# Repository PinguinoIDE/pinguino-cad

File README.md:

Most of the Pinguino boards or extensions are designed with Kicad.

KiCad is an EDA software suite for the creation of professional schematics and printed circuit boards up to 16 layers. KiCad runs on Windows, Linux and Apple OS X and is released under the open-source GNU GPL v2 free of charge. With Kicad you can do the following :

<ul>
<li>Schematic design.
<li>Netlist creation in multiple formats (PCBNew, OrCAD, CadStar, Spice, etc...).
<li>PCB design
<li>3D visualization of your PCB
<li>Fabrication outputs generation (Gerber, drill files and whatever can be needed to manufacture a PCB.)
</ul>

For a more detailed explanation please refer to the official site : http://www.kicad.org

For a better result we use libraries, modules en 3D packages from Walter : http://smisioto.no-ip.org/elettronica/kicad/kicad-en.htm

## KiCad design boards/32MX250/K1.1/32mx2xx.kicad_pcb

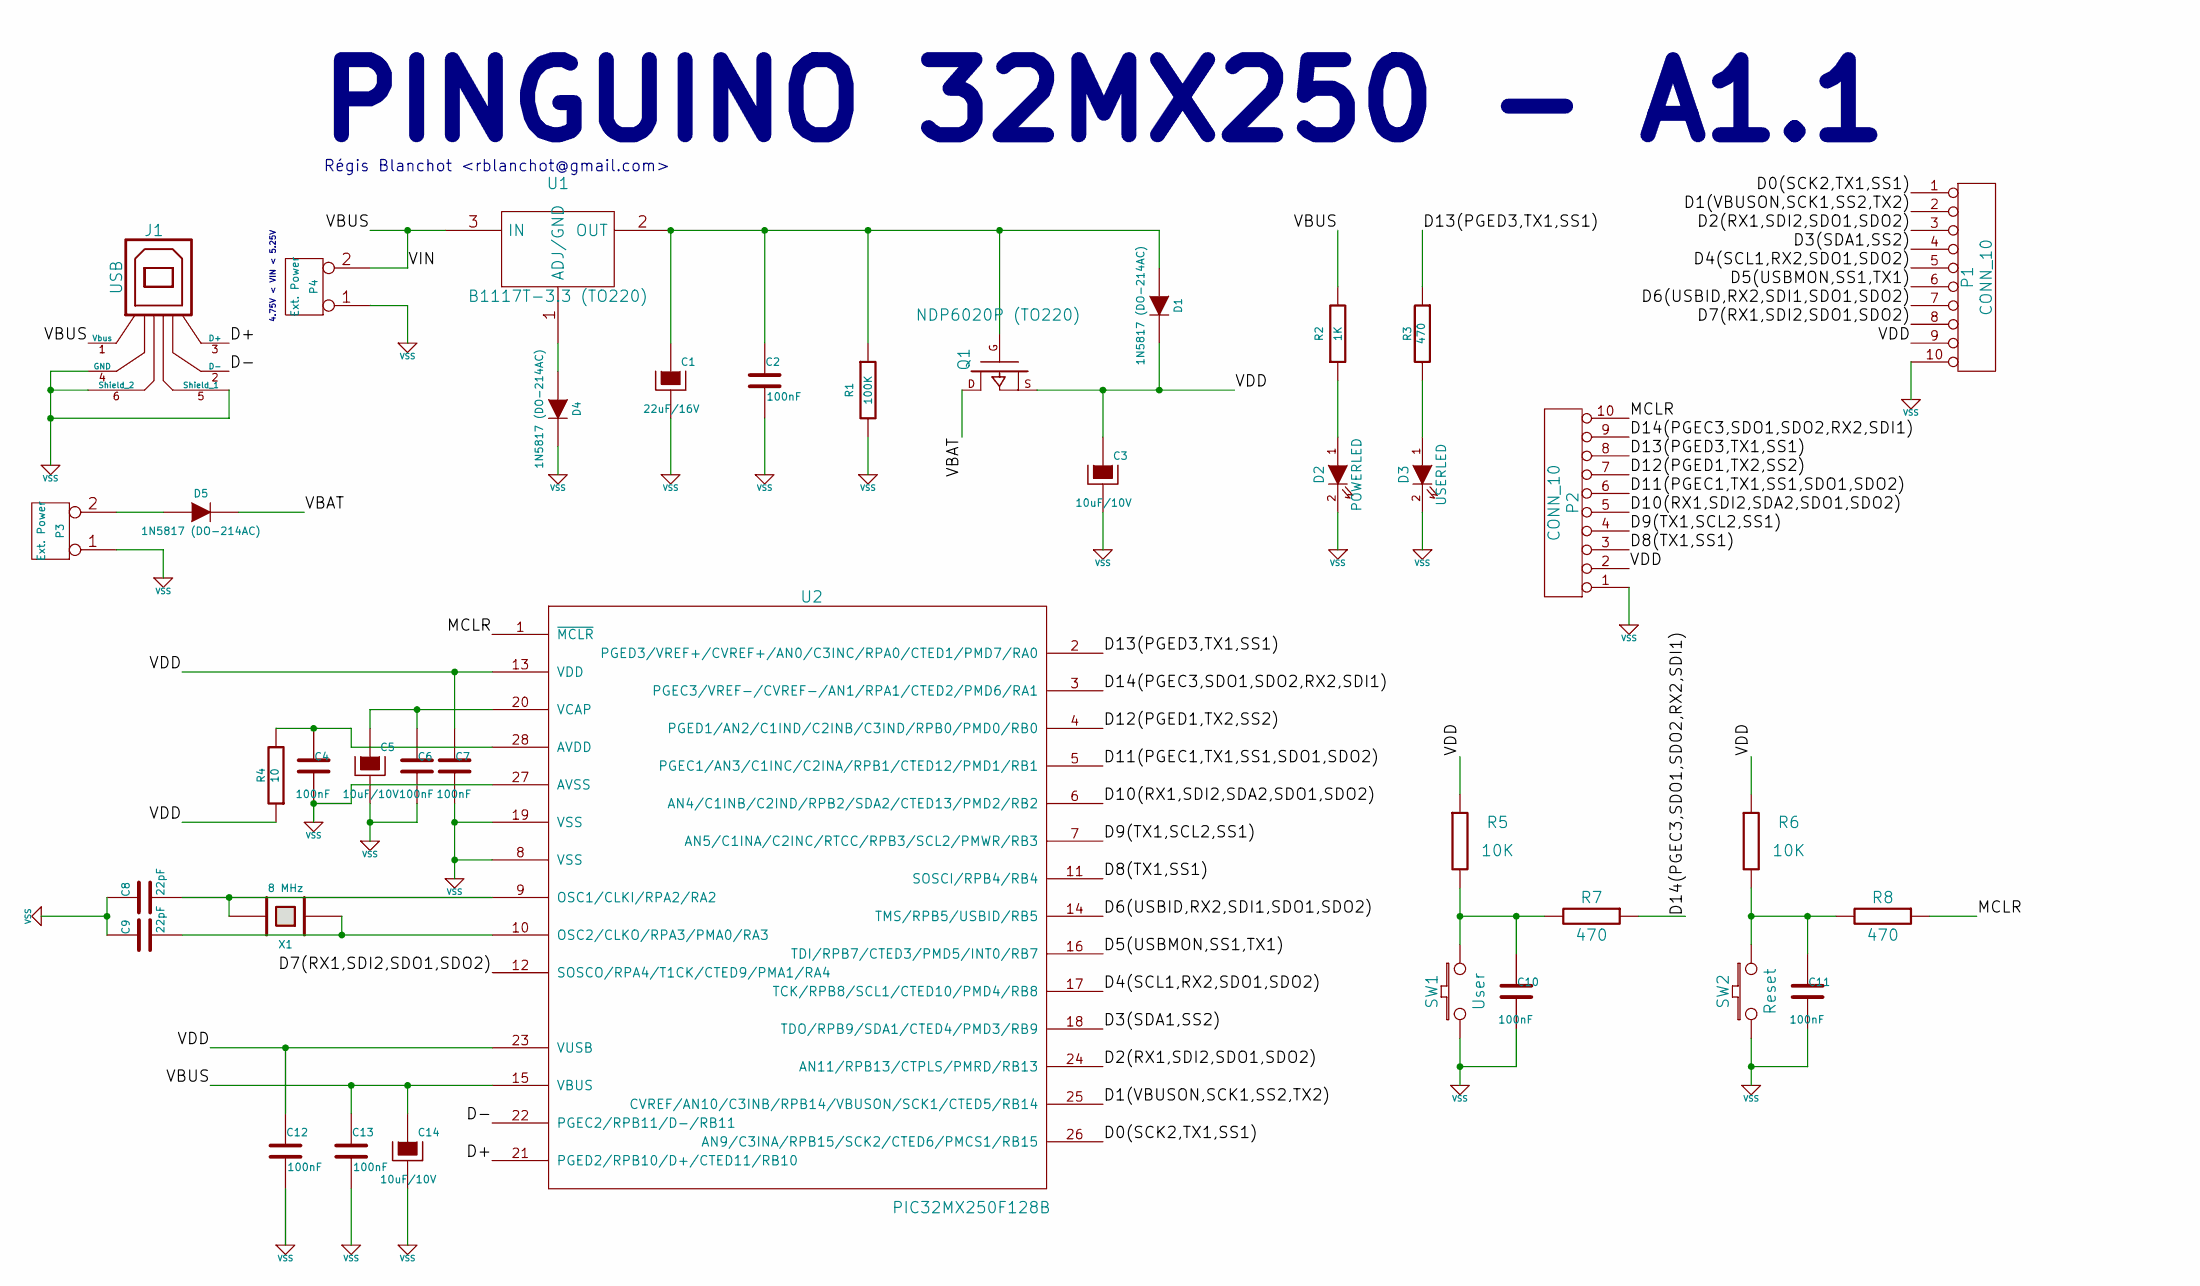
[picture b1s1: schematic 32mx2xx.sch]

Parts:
C1: 22uF/16V
C2, C4, C6, C7, C10, C11, C12, C13: 100nF
C3, C5, C14: 10uF/10V
C8, C9: 22pF
D1, D4, D5: 1N5817 (DO-214AC)
D2: POWERLED
D3: USERLED
J1: USB
P1, P2: CONN_10
P3, P4: Ext. Power
Q1: NDP6020P (TO220)
R1: 100K
R2: 1K
R3: 470
R4: 10
R5, R6: 10K
R7, R8: 470
SW1: User
SW2: Reset
U1: B1117T-3.3 (TO220)
U2: PIC32MX250F128B
X1: 8 MHz

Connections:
/D0(SCK2,TX1,SS1): P1.1, U2.26 (AN9/C3INA/RPB15/SCK2/CTED6/PMCS1/RB15)
/D1(VBUSON,SCK1,SS2,TX2): P1.2, U2.25 (CVREF/AN10/C3INB/RPB14/VBUSON/SCK1/CTED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)
/D2(RX1,SDI2,SDO1,SDO2): P1.3, U2.24 (AN11/RPB13/CTPLS/PMRD/RB13)
/D3(SDA1,SS2): P1.4, U2.18 (TDO/RPB9/SDA1/CTED4/PMD3/RB9)
/D4(SCL1,RX2,SDO1,SDO2): P1.5, U2.17 (TCK/RPB8/SCL1/CTED10/PMD4/RB8)
/D5(USBMON,SS1,TX1): P1.6, U2.16 (TDI/RPB7/CTED3/PMD5/INT0/RB7)
/D6(USBID,RX2,SDI1,SDO1,SDO2): P1.7, U2.14 (TMS/RPB5/USBID/RB5)
/D7(RX1,SDI2,SDO1,SDO2): P1.8, U2.12 (SOSCO/RPA4/T1CK/CTED9/PMA1/RA4)
/D8(TX1,SS1): P2.3, U2.11 (SOSCI/RPB4/RB4)
/D9(TX1,SCL2,SS1): P2.4, U2.7 (AN5/C1INA/C2INC/RTCC/RPB3/SCL2/PMWR/RB3)
/D10(RX1,SDI2,SDA2,SDO1,SDO2): P2.5, U2.6 (AN4/C1INB/C2IND/RPB2/SDA2/CTED13/PMD2/R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)
/D11(PGEC1,TX1,SS1,SDO1,SDO2): P2.6, U2.5 (PGEC1/AN3/C1INC/C2INA/RPB1/CTED12/PMD1/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)
/D12(PGED1,TX2,SS2): P2.7, U2.4 (PGED1/AN2/C1IND/C2INB/C3IND/RPB0/PMD0/R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)
/D13(PGED3,TX1,SS1): P2.8, R3.1, U2.2 (PGED3/VREF+/CVREF+/AN0/C3INC/RPA0/CTED1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)
/D14(PGEC3,SDO1,SDO2,RX2,SDI1): P2.9, R7.1, U2.3 (PGEC3/VREF-/CVREF-/AN1/RPA1/CTED2/PMD6/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)
/D+: J1.3 (D+), U2.21 (PGED2/RPB10/D+/CTED11/RB10)
/D-: J1.2 (D-), U2.22 (PGEC2/RPB11/D-/RB11)
/MCLR: P2.10, R8.1, U2.1 (~MCLR~)
/VBAT: D5.2 (K), Q1.D
/VBUS: C13.1, C14.1, J1.1 (Vbus), P4.2 (PM), R2.2, U1.3 (IN), U2.15 (VBUS)
/VDD: C3.1, C7.1, C12.1, D1.2 (K), P1.9, P2.2, Q1.S, R4.1, R5.1, R6.1, U2.13 (VDD), U2.23 (VUSB)
unnamed: C1.1, C2.1, D1.1 (A), Q1.G, R1.1, U1.2 (OUT)
unnamed: C4.1, R4.2, U2.28 (AVDD)
unnamed: C5.1, C6.1, U2.20 (VCAP)
unnamed: C8.2, U2.9 (OSC1/CLKI/RPA2/RA2), X1.2
unnamed: C9.2, U2.10 (OSC2/CLKO/RPA3/PMA0/RA3), X1.1
unnamed: C10.1, R5.2, R7.2, SW1.2
unnamed: C11.1, R6.2, R8.2, SW2.2
unnamed: D2.1 (A), R2.1
unnamed: D3.1 (A), R3.2
unnamed: D4.1 (A), U1.1 (ADJ/GND)
unnamed: D5.1 (A), P3.2 (PM)
VSS: C1.2, C2.2, C3.2, C4.2, C5.2, C6.2, C7.2, C8.1, C9.1, C10.2, C11.2, C12.2, C13.2, C14.2, D2.2 (K), D3.2 (K), D4.2 (K), J1.4 (GND), J1.5 (Shield_1), J1.6 (Shield_2), P1.10, P2.1, P3.1, P4.1, R1.2, SW1.1, SW2.1, U2.8 (VSS), U2.19 (VSS), U2.27 (AVSS)

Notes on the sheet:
Régis Blanchot <rblanchot@gmail.com>
PINGUINO 32MX250 - A1.1
4.75V < VIN < 5.25V

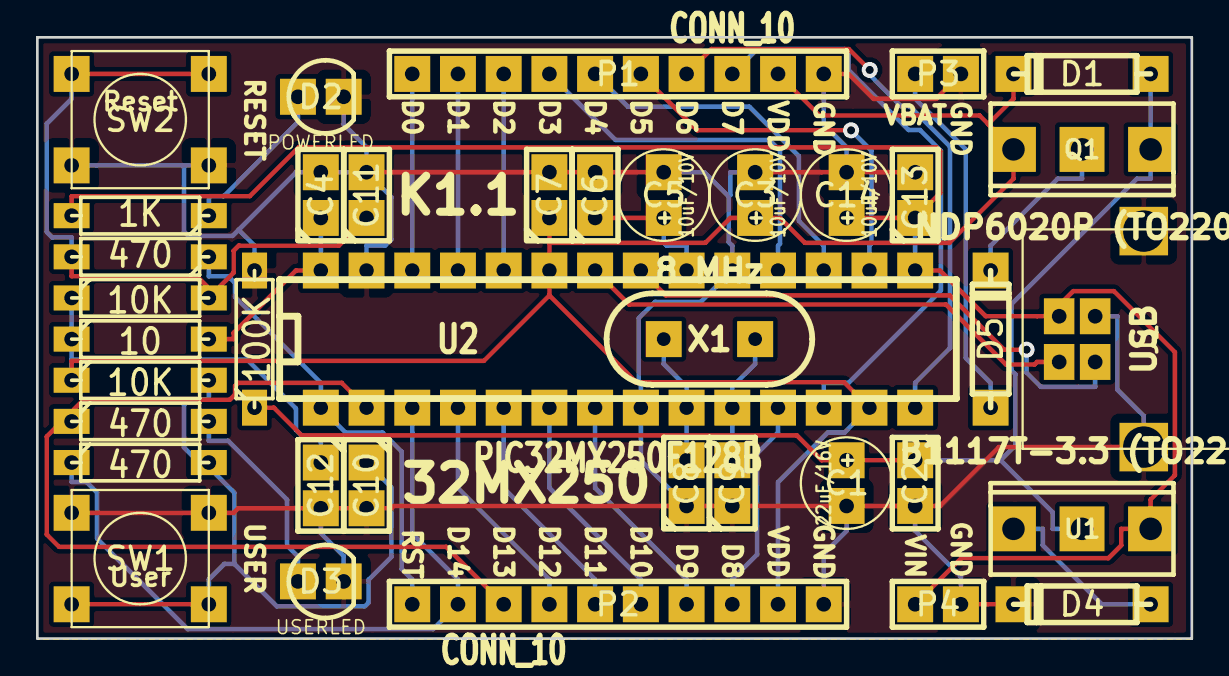
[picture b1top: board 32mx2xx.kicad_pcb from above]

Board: 2 copper layers, 64.1 x 33.4 mm, 40 parts (1 on the bottom side), 33 nets.

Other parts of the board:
G2: LOGO; Logo_silk_OSHW_6x6mm
VAL: logo1in

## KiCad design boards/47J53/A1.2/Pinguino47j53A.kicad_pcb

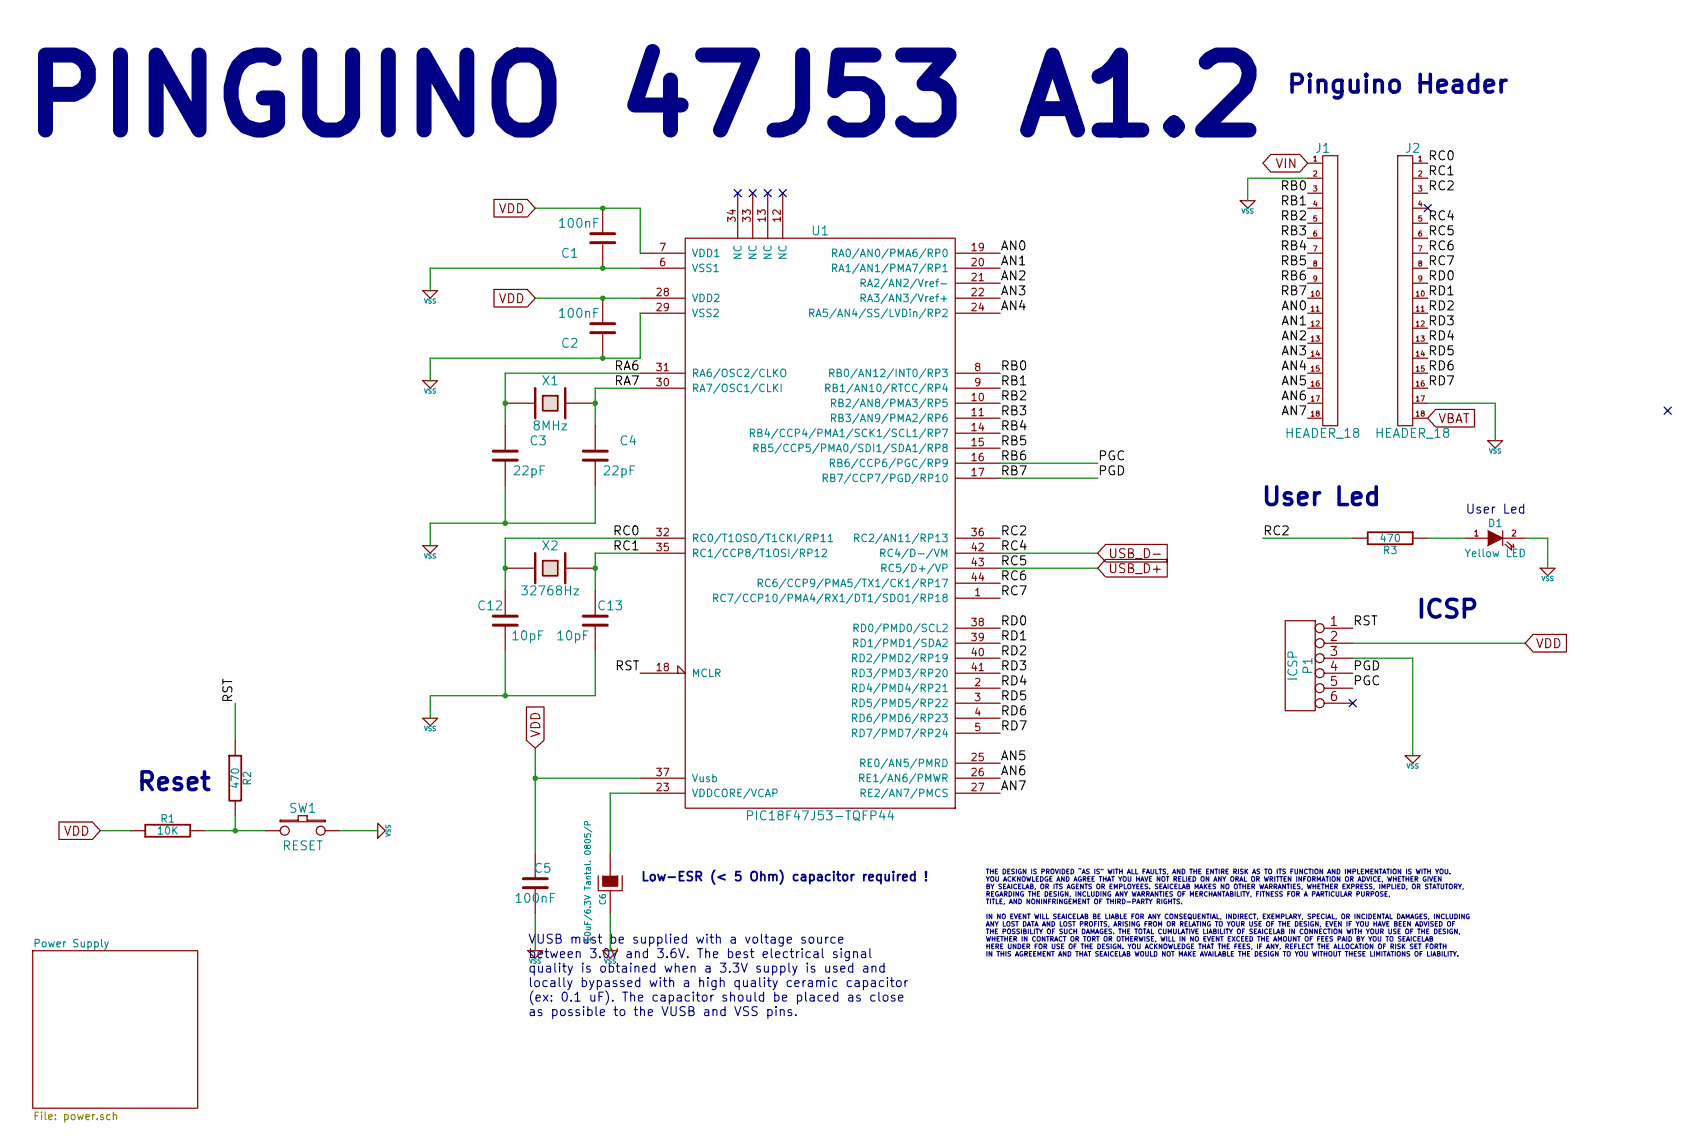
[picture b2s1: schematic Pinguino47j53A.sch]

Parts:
C1, C2, C5: 100nF
C3, C4: 22pF
C6: 10uF/6.3V Tantal. 0805/P
C12, C13: 10pF
D1: Yellow LED
J1, J2: HEADER_18
P1: ICSP
R1: 10K
R2, R3: 470
SW1: RESET
U1: PIC18F47J53-TQFP44
X1: 8MHz
X2: 32768Hz

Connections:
/AN0: J1.11, U1.19 (RA0/AN0/PMA6/RP0)
/AN1: J1.12, U1.20 (RA1/AN1/PMA7/RP1)
/AN2: J1.13, U1.21 (RA2/AN2/Vref-)
/AN3: J1.14, U1.22 (RA3/AN3/Vref+)
/AN4: J1.15, U1.24 (RA5/AN4/SS/LVDin/RP2)
/AN5: J1.16, U1.25 (RE0/AN5/PMRD)
/AN6: J1.17, U1.26 (RE1/AN6/PMWR)
/AN7: J1.18, U1.27 (RE2/AN7/PMCS)
/PGC: J1.9, P1.5, U1.16 (RB6/CCP6/PGC/RP9)
/PGD: J1.10, P1.4, U1.17 (RB7/CCP7/PGD/RP10)
/RA6: C3.1, U1.31 (RA6/OSC2/CLKO), X1.1
/RA7: C4.1, U1.30 (RA7/OSC1/CLKI), X1.2
/RB0: J1.3, U1.8 (RB0/AN12/INT0/RP3)
/RB1: J1.4, U1.9 (RB1/AN10/RTCC/RP4)
/RB2: J1.5, U1.10 (RB2/AN8/PMA3/RP5)
/RB3: J1.6, U1.11 (RB3/AN9/PMA2/RP6)
/RB4: J1.7, U1.14 (RB4/CCP4/PMA1/SCK1/SCL1/RP7)
/RB5: J1.8, U1.15 (RB5/CCP5/PMA0/SDI1/SDA1/RP8)
/RC0: C12.1, J2.1, U1.32 (RC0/T1OSO/T1CKI/RP11), X2.1
/RC1: C13.1, J2.2, U1.35 (RC1/CCP8/T1OSI/RP12), X2.2
/RC2: J2.3, R3.2, U1.36 (RC2/AN11/RP13)
/RC6: J2.7, U1.44 (RC6/CCP9/PMA5/TX1/CK1/RP17)
/RC7: J2.8, U1.1 (RC7/CCP10/PMA4/RX1/DT1/SDO1/RP18)
/RD0: J2.9, U1.38 (RD0/PMD0/SCL2)
/RD1: J2.10, U1.39 (RD1/PMD1/SDA2)
/RD2: J2.11, U1.40 (RD2/PMD2/RP19)
/RD3: J2.12, U1.41 (RD3/PMD3/RP20)
/RD4: J2.13, U1.2 (RD4/PMD4/RP21)
/RD5: J2.14, U1.3 (RD5/PMD5/RP22)
/RD6: J2.15, U1.4 (RD6/PMD6/RP23)
/RD7: J2.16, U1.5 (RD7/PMD7/RP24)
/RST: P1.1, R2.1, U1.18 (MCLR)
unnamed: D1.1 (A), R3.1
unnamed: R1.2, R2.2, SW1.1
unnamed: C6.1, U1.23 (VDDCORE/VCAP)
USB_D+: J2.6, U1.43 (RC5/D+/VP); also elsewhere on the board
USB_D-: J2.5, U1.42 (RC4/D-/VM); also elsewhere on the board
VBAT: J2.18; also elsewhere on the board
VBUS: J1.1; also elsewhere on the board
VDD: C1.2, C2.2, C5.1, P1.2, R1.1, U1.7 (VDD1), U1.28 (VDD2), U1.37 (Vusb); also elsewhere on the board
VSS: C1.1, C2.1, C3.2, C4.2, C5.2, C6.2, C12.2, C13.2, D1.2 (K), J1.2, J2.17, P1.3, SW1.2, U1.6 (VSS1), U1.29 (VSS2); also elsewhere on the board

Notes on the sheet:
VUSB must be supplied with a voltage source between 3.0V and 3.6V. The best electrical signal quality is obtained when a 3.3V supply is used and locally bypassed with a high quality ceramic capacitor (ex: 0.1 uF). The capacitor should be placed as close as possible to the VUSB and VSS pins.
Low-ESR (< 5 Ohm) capacitor required !
PINGUINO 47J53 A1.2
User Led
Reset
THE DESIGN IS PROVIDED “AS IS” WITH ALL FAULTS, AND THE ENTIRE RISK AS TO ITS FUNCTION AND IMPLEMENTATION IS WITH YOU. YOU ACKNOWLEDGE AND AGREE THAT YOU HAVE NOT RELIED ON ANY ORAL OR WRITTEN INFORMATION OR ADVICE, WHETHER GIVEN BY SEAICELAB, OR ITS AGENTS OR EMPLOYEES. SEAICELAB MAKES NO OTHER WA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
ICSP
Pinguino Header

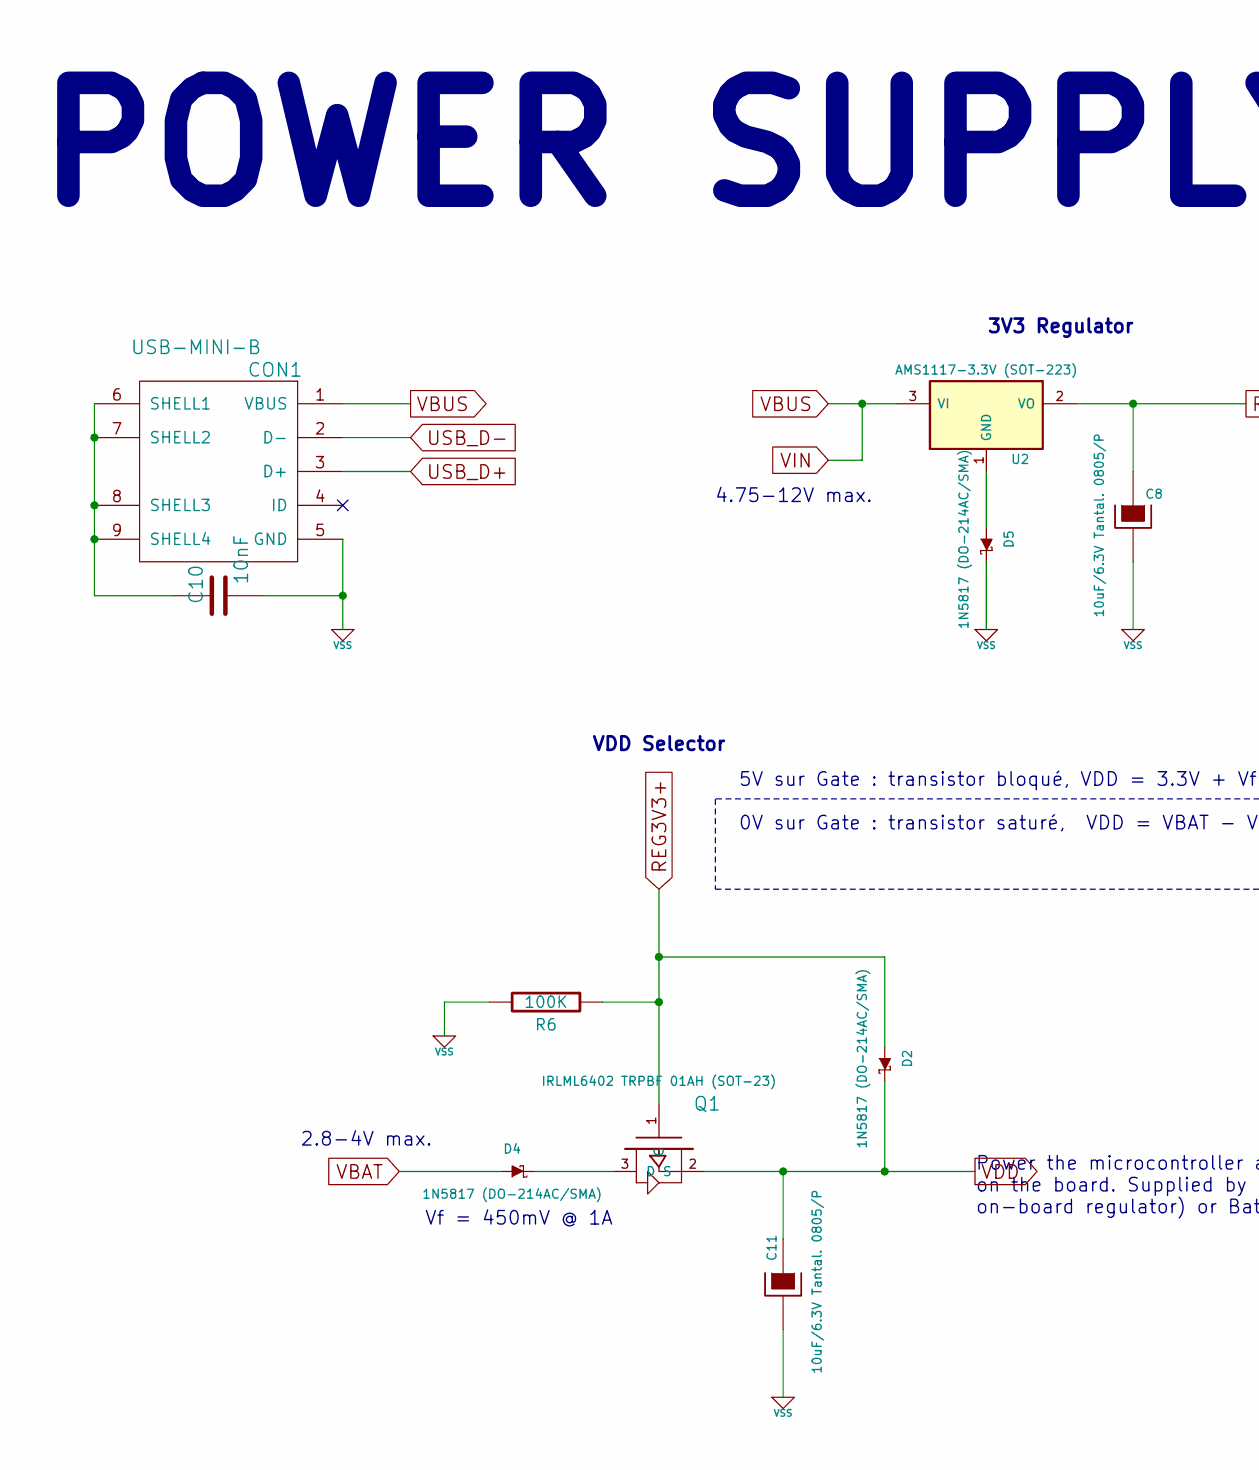
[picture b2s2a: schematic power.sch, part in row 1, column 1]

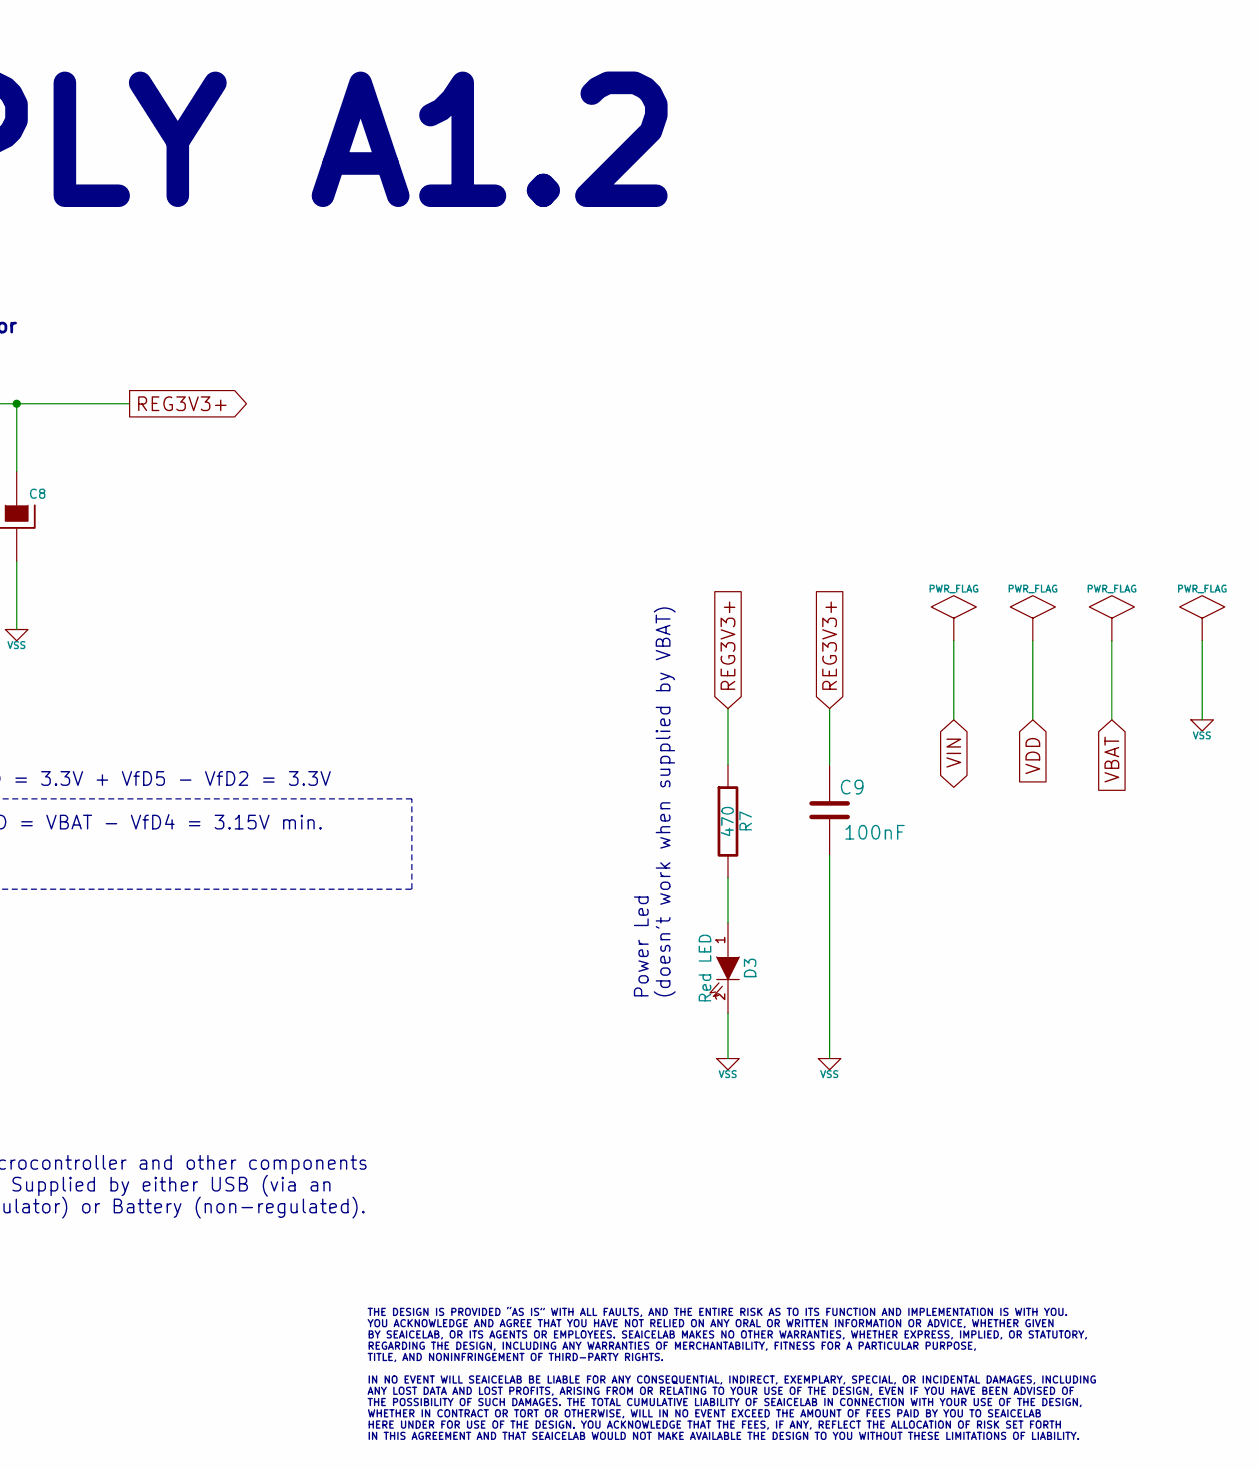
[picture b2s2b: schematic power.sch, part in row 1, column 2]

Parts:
C8, C11: 10uF/6.3V Tantal. 0805/P
C9: 100nF
C10: 10nF
CON1: USB-MINI-B
D2, D4, D5: 1N5817 (DO-214AC/SMA)
D3: Red LED
Q1: IRLML6402 TRPBF 01AH (SOT-23)
R6: 100K
R7: 470
U2: AMS1117-3.3V (SOT-223)

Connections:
unnamed: D5.1 (A), U2.1 (GND)
unnamed: D4.2 (K), Q1.3 (D)
unnamed: C10.1, CON1.6 (SHELL1), CON1.7 (SHELL2), CON1.8 (SHELL3), CON1.9 (SHELL4)
unnamed: D3.1 (A), R7.2
REG3V3+: C8.1, C9.2, D2.1 (A), Q1.1 (G), R6.1, R7.1, U2.2 (VO)
USB_D+: CON1.3 (D+); also elsewhere on the board
USB_D-: CON1.2 (D-); also elsewhere on the board
VBAT: D4.1 (A); also elsewhere on the board
VBUS: CON1.1 (VBUS), U2.3 (VI); also elsewhere on the board
VDD: C11.1, D2.2 (K), Q1.2 (S); also elsewhere on the board
VSS: C8.2, C9.1, C10.2, C11.2, CON1.5 (GND), D3.2 (K), D5.2 (K), R6.2; also elsewhere on the board

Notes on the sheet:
Vf = 450mV @ 1A
2.8-4V max.
Power the microcontroller and other components on the board. Supplied by either USB (via an on-board regulator) or Battery (non-regulated).
THE DESIGN IS PROVIDED “AS IS” WITH ALL FAULTS, AND THE ENTIRE RISK AS TO ITS FUNCTION AND IMPLEMENTATION IS WITH YOU. YOU ACKNOWLEDGE AND AGREE THAT YOU HAVE NOT RELIED ON ANY ORAL OR WRITTEN INFORMATION OR ADVICE, WHETHER GIVEN BY SEAICELAB, OR ITS AGENTS OR EMPLOYEES. SEAICELAB MAKES NO OTHER WA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
VDD Selector
POWER SUPPLY A1.2
Power Led (doesn't work when supplied by VBAT)
5V sur Gate : transistor bloqué, VDD = 3.3V + VfD5 - VfD2 = 3.3V 0V sur Gate : transistor saturé, VDD = VBAT - VfD4 = 3.15V min.
3V3 Regulator
4.75-12V max.

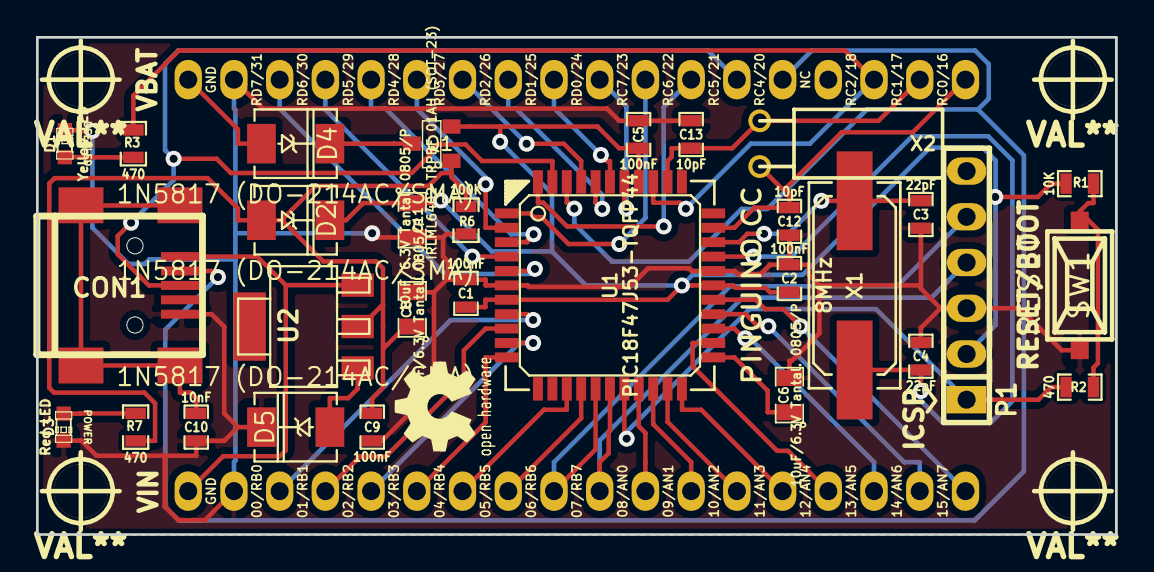
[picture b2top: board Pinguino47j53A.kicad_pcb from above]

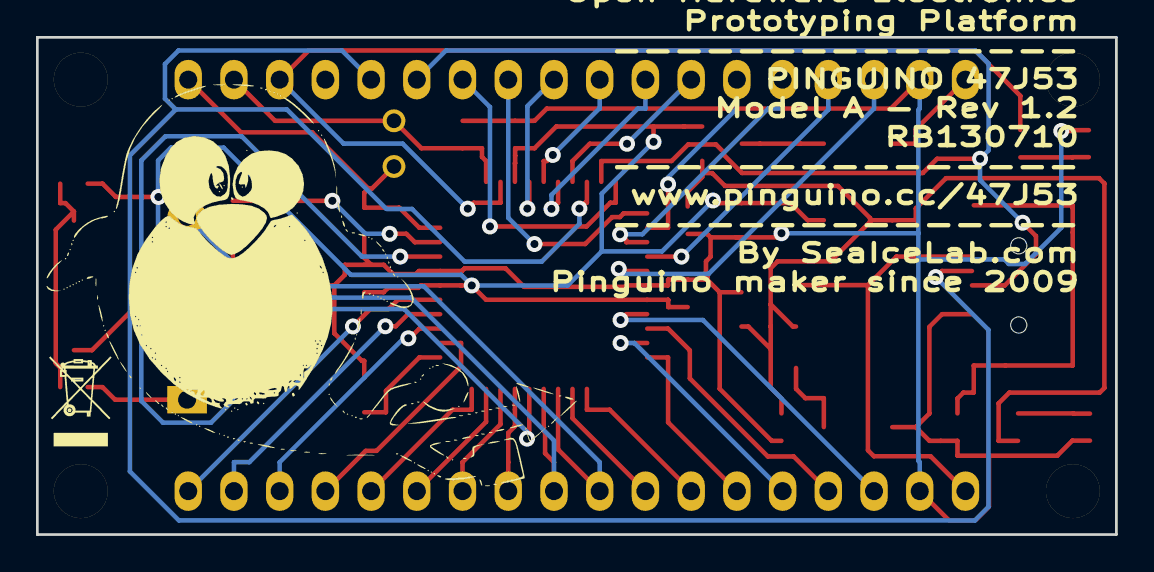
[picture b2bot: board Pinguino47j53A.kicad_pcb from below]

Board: 2 copper layers, 59.9 x 27.6 mm, 38 parts (4 on the bottom side), 46 nets.

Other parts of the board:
G1: LOGO
G2: LOGO; Logo_silk_WEEE_3.4x5mm
hole_3mm_1, hole_3mm_2, hole_3mm_3, hole_3mm_4: VAL**; hole_3mm

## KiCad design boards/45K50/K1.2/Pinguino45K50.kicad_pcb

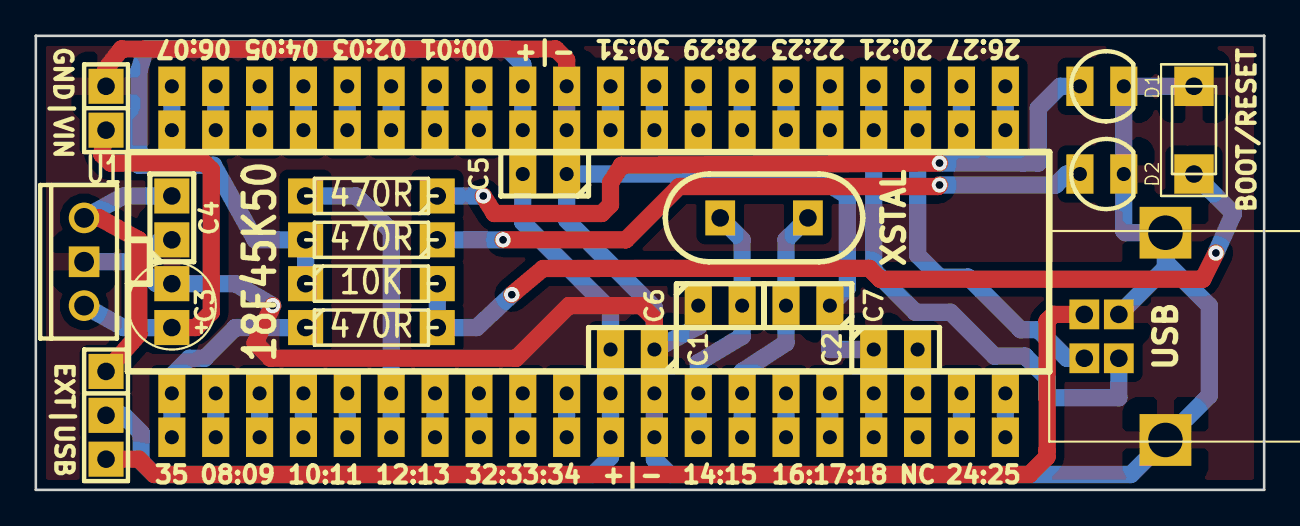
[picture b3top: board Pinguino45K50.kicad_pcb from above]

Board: 2 copper layers, 71.1 x 26.3 mm, 23 parts (1 on the bottom side), 44 nets.

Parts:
C1, C4, C5: 100nF/63V (104); C1
C2: 220nF/63V (224); C1
C3: CP1; C1V5
C6, C7: 22pF; C1
D1: USERLED; LED-3MM
D2: POWERLED; LED-3MM
JP1: USB; USB_B
K1: Selector; Pin_Header_Straight_1x03
P0: Power; Pin_Header_Straight_1x02
P1: left; Pin_Header_Straight_1x20
P2: right; Pin_Header_Straight_1x20
R1, R2, R4: 470R; R3
R3: 10K; R3
SW1: Reset; SW_PUSH_SMALL
Sym: Symbol_OSHW-Logo_SilkScreen_BIG_07Jul2012; Symbol_OSHW-Logo_SilkScreen_BIG
U1: 7805; LM78XXV
U***1: 18F45K50; DIP-40__600_ELL
X1: XSTAL; HC-49V

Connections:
5V: C4.2, K1.1, U1.VO
/CS: P1.7, U***1.7
/D+: JP1.3, P2.17, U***1.24
/D-: JP1.2, P2.18, U***1.23
/MCLR: P1.1, R4.1, U***1.1
/OSC1: C6.2, P1.13, U***1.13, X1.2
/OSC2: C7.2, P1.14, U***1.14, X1.1
/PGC: P2.2, U***1.39
/PGD: P2.1, U***1.40
/PGM: P2.3, U***1.38
/RA0: P1.2, U***1.2
/RA1: P1.3, U***1.3
/RA2: P1.4, U***1.4
/RA3: P1.5, U***1.5
/RA4: P1.6, R1.2, U***1.6
/RB0: P2.8, U***1.33
/RB1: P2.7, U***1.34
/RB2: P2.6, U***1.35
/RB3: P2.5, U***1.36
/RB4: P2.4, U***1.37
/RC0: P1.15, U***1.15
/RC1: P1.16, U***1.16
/RC2: P1.17, U***1.17
/RC6: P2.16, U***1.25
/RC7: P2.15, U***1.26
/RD0: P1.19, U***1.19
/RD1: P1.20, U***1.20
/RD2: P2.20, U***1.21
/RD3: P2.19, U***1.22
/RD4: P2.14, U***1.27
/RD5: P2.13, U***1.28
/RD6: P2.12, U***1.29
/RD7: P2.11, U***1.30
/RE0: P1.8, U***1.8
/RE1: P1.9, U***1.9
/RE2: P1.10, U***1.10
unnamed: C2.2, U***1.18
unnamed: C3.1, P0.1, U1.VI
unnamed: D1.1, R1.1
unnamed: D2.1, R2.1
unnamed: R3.2, R4.2, SW1.2
VDD: C1.2, C5.2, K1.2, P1.11, P2.9, R2.2, R3.1, U***1.11, U***1.32
VSS: C1.1, C2.1, C3.2, C4.1, C5.1, C6.1, C7.1, D1.2, D2.2, JP1.4, JP1.5, JP1.6, P0.2, P1.12, P2.10, SW1.1, U1.GND, U***1.12, U***1.31
VUSB: JP1.1, K1.3

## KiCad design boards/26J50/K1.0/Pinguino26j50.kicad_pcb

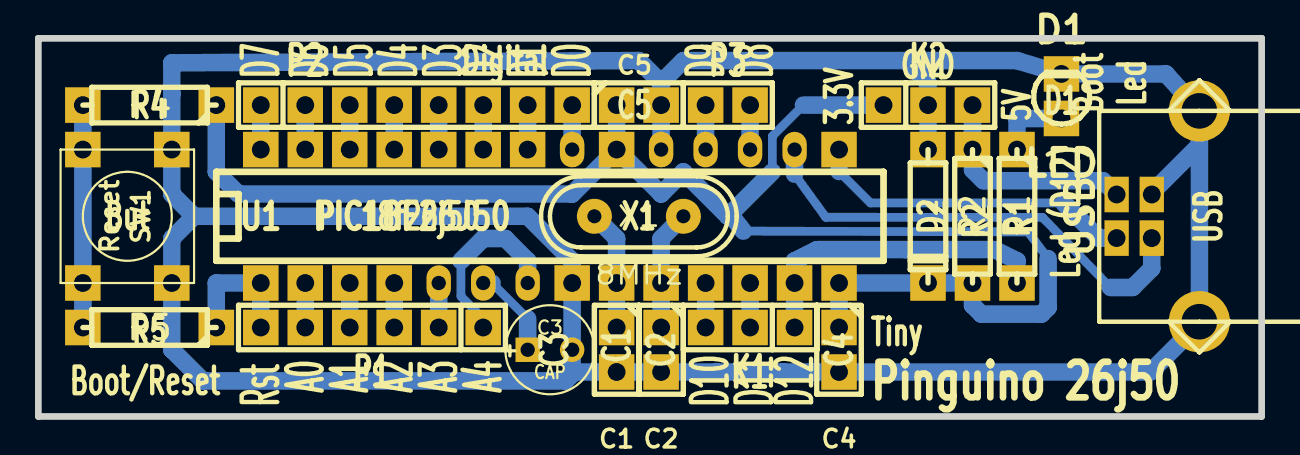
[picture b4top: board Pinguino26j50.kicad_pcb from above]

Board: 2 copper layers, 69.9 x 21.6 mm, 20 parts (0 on the bottom side), 29 nets.

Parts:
C1, C2: 22pF; cnp_3mm_disc
C3: CAP; C1V5
C4, C5: 100nF; cnp_3mm_disc
D1: LED; led_3mm_red
D2: BZX85C3V3; D3
JP1: USB; conn_usb_B
K1: PWM; SIL-3
K2: Power; SIL-3
P1: Analog; SIL-6
P2: Digital; SIL-8
P3: UART; SIL-2
R1: 390; R3
R2: 5.6; R3
R4: 10K; R3
R5: 390R; R3
SW1: Reset; SW_PUSH_SMALL
U1: PIC18F26J50; DIP-28__300
X1: 8MHz; crystal_hc-49u

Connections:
3.3V: C4.1, C5.1, D2.2, K2.1, R2.2, R4.1, U1.14, U1.20
5V: JP1.1, K2.3, R2.1
D+: JP1.3, U1.16
D-: JP1.2, U1.15
GND: C1.2, C2.2, C3.2, C4.2, C5.2, D1.2, D2.1, JP1.4, JP1.5, JP1.6, K2.2, SW1.1, U1.8, U1.19
unnamed: P2.2, U1.27
unnamed: P2.4, U1.25
unnamed: P2.6, U1.23
unnamed: D1.1, R1.1
unnamed: P1.1, U1.7
unnamed: K1.1, R1.2, U1.13
unnamed: P2.3, U1.26
unnamed: P3.2, U1.17
unnamed: P3.1, U1.18
unnamed: P2.1, U1.28
unnamed: P2.5, U1.24
unnamed: C2.1, U1.10, X1.2
unnamed: P1.5, U1.2
unnamed: P1.4, U1.3
unnamed: P1.2, U1.5
unnamed: C1.1, U1.9, X1.1
unnamed: C3.1, U1.6
unnamed: K1.3, U1.11
unnamed: P2.8, U1.21
unnamed: K1.2, U1.12
unnamed: P2.7, U1.22
unnamed: P1.3, U1.4
unnamed: R4.2, R5.2, SW1.2
reset: P1.6, R5.1, U1.1

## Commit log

2014-02-11 added README.md
2014-02-11 new file: LICENSE new file: boards/26J50/K1.0/$savepcb.000 new file: boards/26J50/K1.0/$savepcb.brd new file: boards/26J50/K1.0/BoM.odt new file: boards/26J50/K1.0/Pinguino26j50-Contours_PCB.gbr new 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
2014-07-08 Added New Pinguino 45K50 CAD Files
2021-04-24 feat(3d): Added 3D image for 32MX250 and 47J53 boards
2021-11-10 Update README.md
    https://forum.kicad.info/t/warning-avoid-all-links-to-kicad-pcb-org-use-kicad-org/31521
